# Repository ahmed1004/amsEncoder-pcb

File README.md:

# AS5048B Breakout Board
## Description
This is a printed circuit board to break out the [AS5048B](http://www.ams.com/eng/Products/Magnetic-Position-Sensors/Rotary-Magnetic-Position-Sensors/AS5048B) rotary encoder to a four-pin I2C connection. This chip returns a 14-bit absolute radial position. The PCB also provides holes for two alignment pins, the CAD for which is given in AS5048B_Encoder_Board.dxf.

##Usage
### Mechanical
The AS5048B reads the absolute radial position of a diametrically polarized magnet which rotates above the center of the chip (center marked by yellow 'X' in dxf). Many magnet configurations can be used, we have found success with a 3mm diameter N52 magnet positioned 2mm away from the die surface of the chip. More detailed application notes are available in the [datasheet](http://www.ams.com/eng/content/download/250006/975176/143016)
### Electronics
The board needs to be populated with the AS5048B, as well as a 10μF 603 surface mount capacitor. There are pads for *SDA* *SCL* *Vcc* and *GND* on the top and bottom of the PCB, for daisy-chaining several boards together. There are pads on the back of the chip for mounting an optional [6-pin Molex connector](http://www.molex.com/molex/products/datasheet.jsp?part=active/5034800600_FFC_FPC_CONNECTORS.xml&channel=Products&Lang=en-US)

Two solder jumpers on the back of the board set the 7-bit I2C address of the chip to be:

        0b10000 A2 A1

Where A1 and A2 are the logical values of the solder-bridged jumpers.
###Code
ams-enc in [imageproc-lib](https://github.com/biomimetics/imageproc-lib) is example code to communicate with the chip. This code uses a blocking read, which is a bit of a faux-pas in a real time loop. For an example of an asynchronous update, see a different version of ams-enc in [my repository.](https://github.com/dhaldane/imageproc-lib)

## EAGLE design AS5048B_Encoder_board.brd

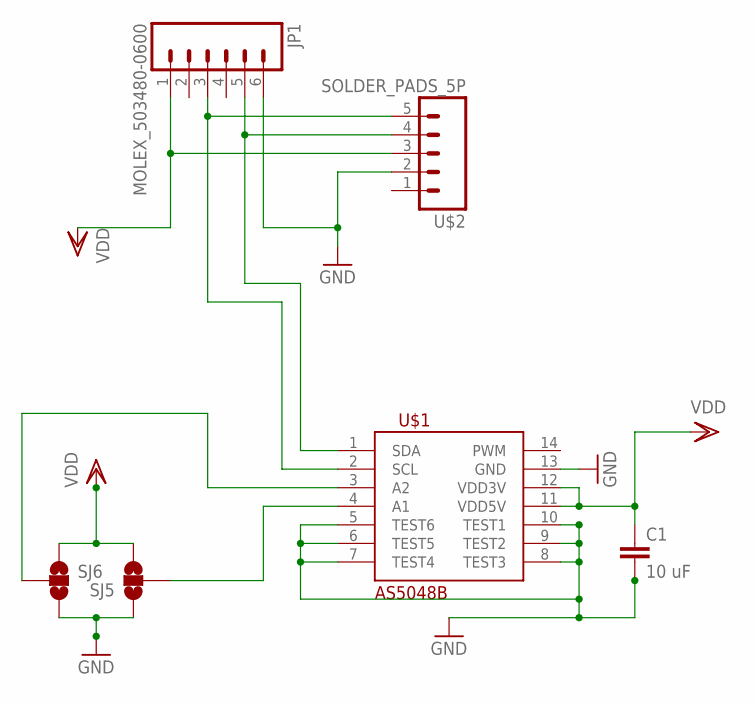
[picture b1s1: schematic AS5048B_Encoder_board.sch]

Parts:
C1: 10 uF; 0603-CAP
JP1: MOLEX_503480-0600
SJ5, SJ6: SOLDERJUMPER_2WAYS; SJ_3
U$1: AS5048B; TSSOP14
U$2: SOLDER_PADS_5P

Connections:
A1: SJ5.2, U$1.4 (A1)
A2: SJ6.2, U$1.3 (A2)
GND: C1.2, JP1.6, SJ5.1, SJ6.3, U$1.5 (TEST6), U$1.6 (TEST5), U$1.7 (TEST4), U$1.8 (TEST3), U$1.9 (TEST2), U$1.10 (TEST1), U$1.13 (GND), U$2.2
SCL: JP1.3, U$1.2 (SCL), U$2.5
SDA: JP1.5, U$1.1 (SDA), U$2.4
VDD: C1.1, JP1.1, SJ5.3, SJ6.1, U$1.11 (VDD5V), U$1.12 (VDD3V), U$2.3

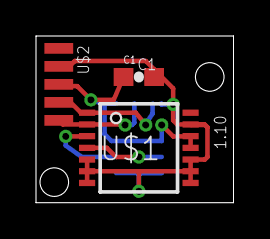
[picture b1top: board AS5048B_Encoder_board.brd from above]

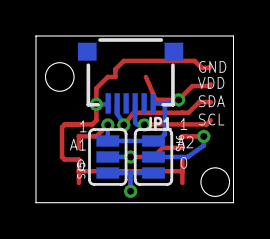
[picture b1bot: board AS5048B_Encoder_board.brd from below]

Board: 2 copper layers, 11.0 x 9.3 mm, 6 parts (3 on the bottom side), 6 nets.

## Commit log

2013-06-20 Initial commit of files

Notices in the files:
parts and their libraries:
SparkFun: Licensing: CC v3.0 Share-Alike You are welcome to use this library for commercial purposes.
